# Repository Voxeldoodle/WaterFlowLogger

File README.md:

# WaterFlowLogger
 Arduino Code for Water Flow logging activities through multiple channels (3).
 
 Librerie necessarie per logger(installabili cercando da gestione librerie da Arduino IDE):
- Arduino megaAVR boards (x comunicare con scheda. Basta cercare nano every e dovrebbe comparire)
- RTClib by adafruit (x modulo RTC)
- u8g2 by oliver (x schermo)

 Schema circuito mancate al momento, ma verrà eventualmente aggiunto in futuro.

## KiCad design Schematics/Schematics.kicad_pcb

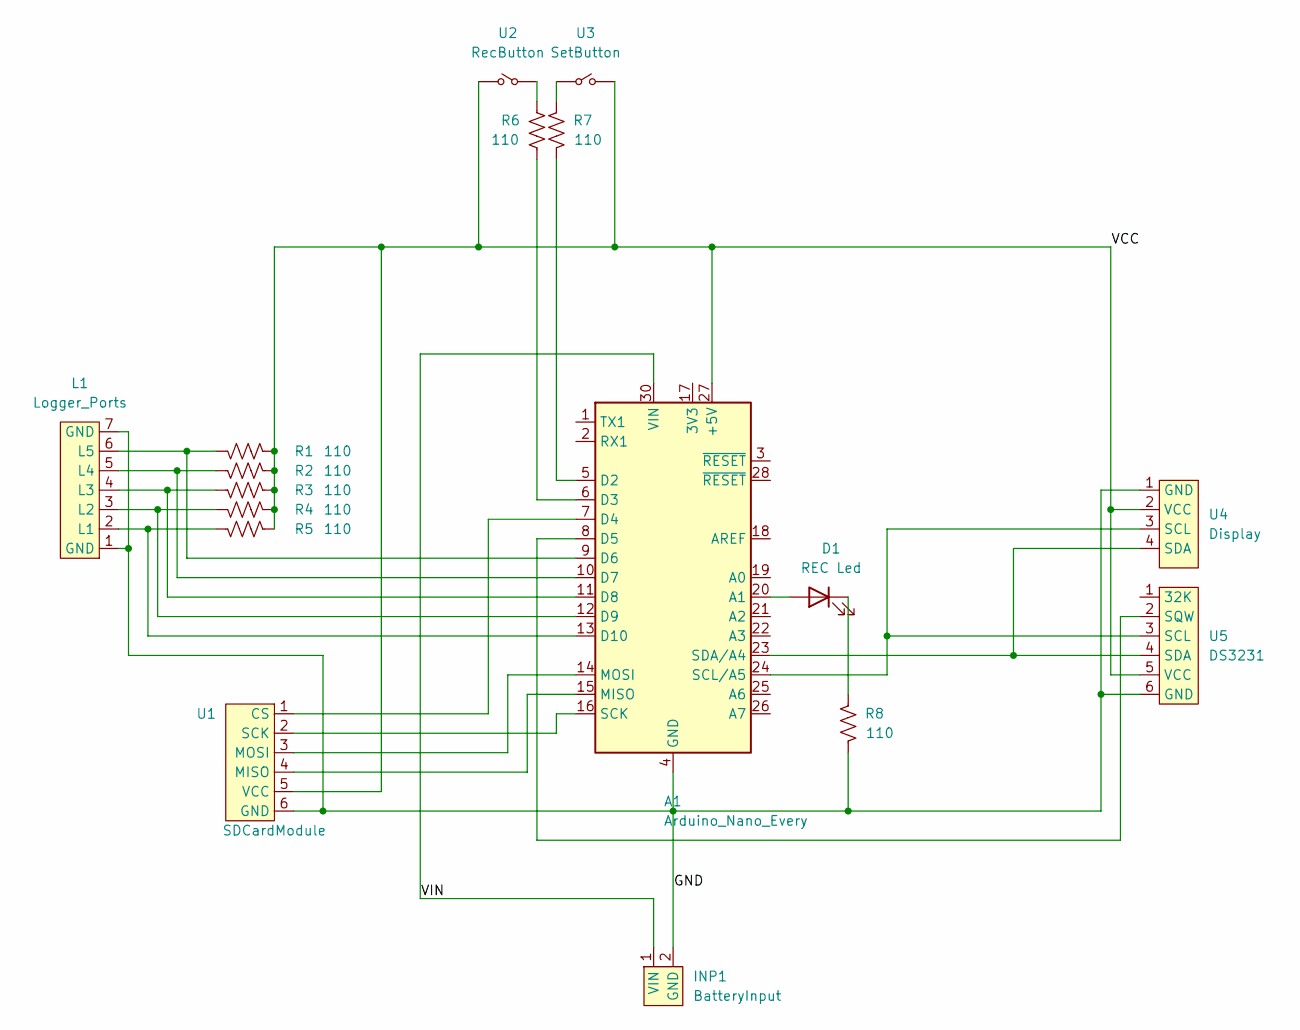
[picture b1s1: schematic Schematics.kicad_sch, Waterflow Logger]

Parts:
A1: Arduino_Nano_Every; Arduino_Nano
D1: REC Led; LED_Oval_W5.2mm_H3.8mm
INP1: BatteryInput; TerminalBlock_4Ucon_1x02_P3.50mm_Horizontal
L1: Logger_Ports; TerminalBlock_4Ucon_1x07_P3.50mm_Vertical
R1, R2, R3, R4, R5, R6, R7, R8: 110; R_Axial_DIN0204_L3.6mm_D1.6mm_P5.08mm_Horizontal
U1: SDCardModule; PinSocket_1x06_P2.54mm_Vertical
U2: RecButton; TerminalBlock_4Ucon_1x02_P3.50mm_Horizontal
U3: SetButton; TerminalBlock_4Ucon_1x02_P3.50mm_Horizontal
U4: Display; TerminalBlock_4Ucon_1x04_P3.50mm_Horizontal
U5: DS3231; PinSocket_1x06_P2.54mm_Vertical

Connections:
/GND: A1.4 (GND), A1.29 (GND), INP1.2 (GND), L1.1 (GND), L1.7 (GND), R8.1, U1.6 (GND), U4.1 (GND), U5.6 (GND)
/VCC: A1.27 (+5V), R1.2, R2.2, R3.2, R4.2, R5.2, U1.5 (VCC), U2.2, U3.2, U4.2 (VCC), U5.5 (VCC)
/VIN: A1.30 (VIN), INP1.1 (VIN)
unnamed: A1.5 (D2), R7.1
unnamed: A1.6 (D3), R6.1
unnamed: A1.7 (D4), U1.1 (CS)
unnamed: A1.8 (D5), U5.2 (SQW)
unnamed: A1.9 (D6), L1.6 (L5), R1.1
unnamed: A1.10 (D7), L1.5 (L4), R2.1
unnamed: A1.11 (D8), L1.4 (L3), R3.1
unnamed: A1.12 (D9), L1.3 (L2), R4.1
unnamed: A1.13 (D10), L1.2 (L1), R5.1
unnamed: A1.14 (MOSI), U1.3 (MOSI)
unnamed: A1.15 (MISO), U1.4 (MISO)
unnamed: A1.16 (SCK), U1.2 (SCK)
unnamed: A1.20 (A1), D1.2 (A)
unnamed: A1.23 (SDA/A4), U4.4 (SDA), U5.4 (SDA)
unnamed: A1.24 (SCL/A5), U4.3 (SCL), U5.3 (SCL)
unnamed: D1.1 (K), R8.2
unnamed: R6.2, U2.1
unnamed: R7.2, U3.1

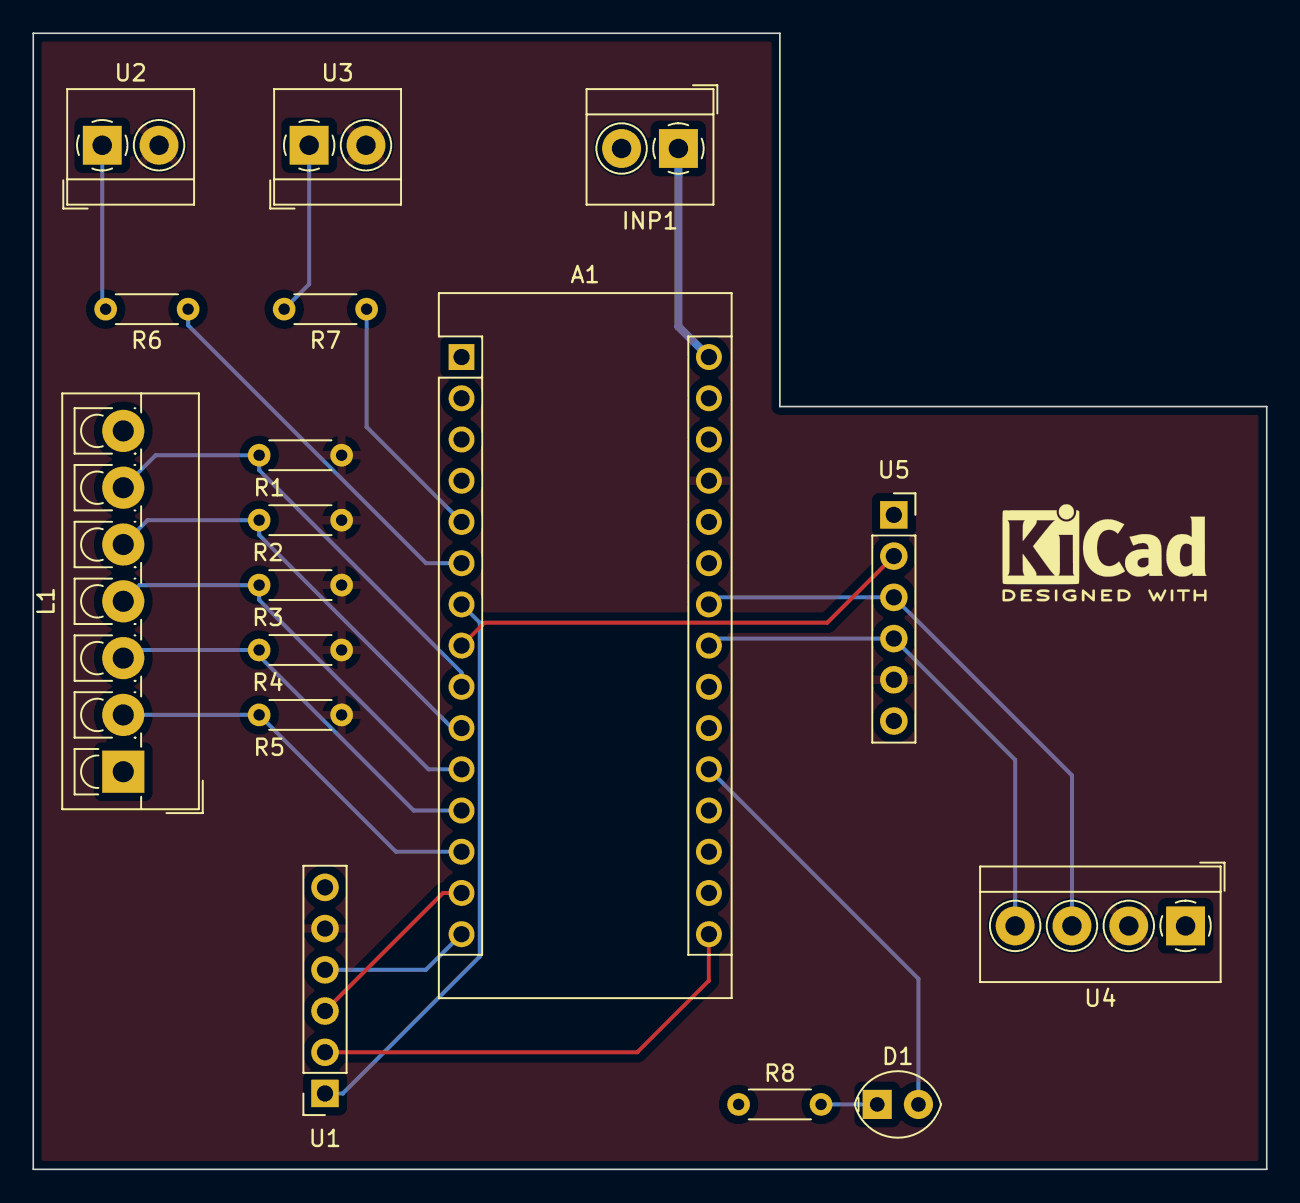
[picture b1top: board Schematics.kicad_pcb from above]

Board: 2 copper layers, 76.0 x 70.0 mm, 17 parts (0 on the bottom side), 21 nets.

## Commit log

2022-01-29 Added Pref + Fix for Flow calc
2022-02-03 Fixed Pref (Hopefully)
2022-02-03 typo
2022-02-06 Fixed missing assignment
2022-02-09 Fixed Bugs + Corrected Debug
2022-02-13 Circuit Schematics + PCB
2022-02-18 Updated PCB
2022-03-04 Updated Flow calc
2022-03-06 Update logger.ino
    Display Stable Flow in interval
